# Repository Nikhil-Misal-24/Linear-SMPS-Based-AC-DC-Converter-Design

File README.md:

🔌 AC to DC Converter – PCB Design Project (Detailed Overview)

This project presents the end-to-end design, simulation, and fabrication of a robust AC to DC power supply system, engineered to convert standard 230V AC mains into a stable and regulated DC output suitable for modern electronic applications.

The design emphasizes efficiency, safety, compactness, and reliability, making it ideal for powering sensitive electronic circuits such as microcontrollers, IoT modules, and embedded systems.

⚙️ Working Principle

The system follows a multi-stage power conversion architecture:

Step-Down Stage
High-voltage AC (230V) is reduced to a safer low voltage using a step-down transformer or SMPS module.
Rectification Stage
A bridge rectifier (using 4 diodes) converts the AC signal into a pulsating DC waveform.
Filtering Stage
Large electrolytic capacitors smooth the pulsating DC, reducing ripple and improving signal stability.
Regulation Stage
Voltage regulators like LM7805, LM7812, or LM317 ensure a constant output voltage, irrespective of input fluctuations.
Protection Stage
Includes fuses, current limiting resistors, and thermal shutdown mechanisms to protect against:
Overcurrent
Short circuits
Overheating

✨ Key Features

✔️ Converts 230V AC → Stable DC output (5V / 12V / Adjustable)

✔️ Low ripple output with effective filtering

✔️ Built-in voltage regulation

✔️ Overcurrent & short-circuit protection

✔️ Compact and optimized PCB layout

✔️ Designed for real-world deployment

🧰 Tools & Technologies Used

🖥️ Design Software

KiCad / Eagle / Altium Designer for schematic & PCB layout
ERC & DRC checks for error-free design

🔬 Testing & Debugging

Multimeter – Voltage & continuity testing
Oscilloscope – Ripple and waveform analysis
🔧 Fabrication

PCB etching / manufacturing
Soldering (Through-hole / SMD components)
📐 PCB Design Highlights

Proper ground plane design for noise reduction

Thermal management (heat sinks for regulators)

Track width optimization for high current paths

Isolation between high-voltage AC and low-voltage DC sections

Compact and single-layer / double-layer PCB options

🚀 Applications

🔹 Embedded Systems Power Supply

🔹 IoT Devices (ESP32, Raspberry Pi, sensors)

🔹 Microcontroller Projects (Arduino, PIC, AVR)

🔹 Robotics Circuits

🔹 DIY Electronics Labs

📊 Performance Considerations

Efficiency depends on topology (Linear vs SMPS)

Ripple voltage minimized using high-value capacitors

Heat dissipation handled via heat sinks

Load regulation tested across different current levels

🔮 Future Improvements

Integration of Switch Mode Power Supply (SMPS) for higher efficiency

Addition of digital voltage/current display

PCB miniaturization using SMD components

Smart protection using microcontroller-based monitoring

📌 Conclusion

This project demonstrates a practical implementation of power electronics concepts, combining analog circuit design, PCB layout, and hardware testing into a real-world solution. It serves as a foundational building block for advanced electronic systems and product development.

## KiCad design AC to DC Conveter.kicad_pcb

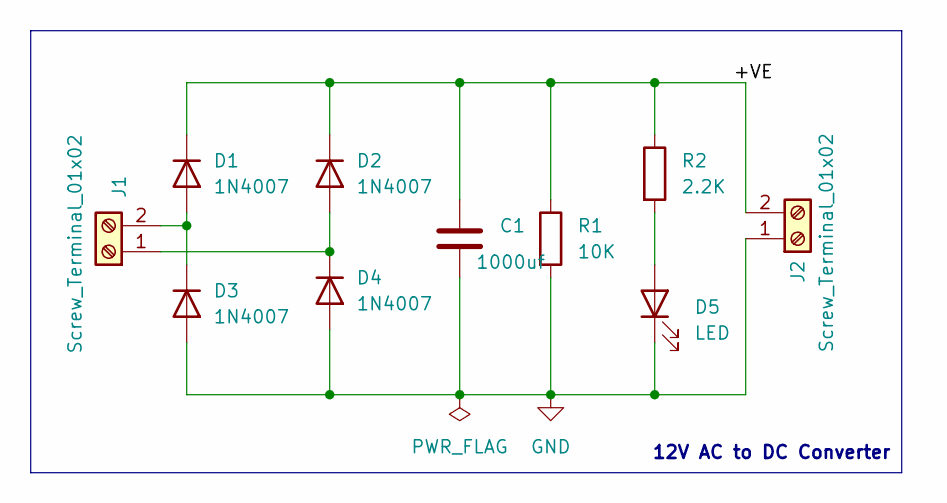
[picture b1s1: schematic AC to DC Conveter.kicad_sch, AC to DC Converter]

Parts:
C1: 1000uf; CP_Radial_D8.0mm_P2.50mm
D1, D2, D3, D4: 1N4007; D_DO-41_SOD81_P10.16mm_Horizontal
D5: LED; LED_D5.0mm
J1, J2: Screw_Terminal_01x02; TerminalBlock_bornier-2_P5.08mm
R1: 10K; R_Axial_DIN0204_L3.6mm_D1.6mm_P7.62mm_Horizontal
R2: 2.2K; R_Axial_DIN0204_L3.6mm_D1.6mm_P7.62mm_Horizontal

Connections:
/+VE: C1.1, D1.1 (K), D2.1 (K), J2.2, R1.1, R2.1
GND: C1.2, D3.2 (A), D4.2 (A), D5.1 (K), J2.1, R1.2
unnamed: D1.2 (A), D3.1 (K), J1.2
unnamed: D2.2 (A), D4.1 (K), J1.1
unnamed: D5.2 (A), R2.2

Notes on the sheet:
12V AC to DC Converter

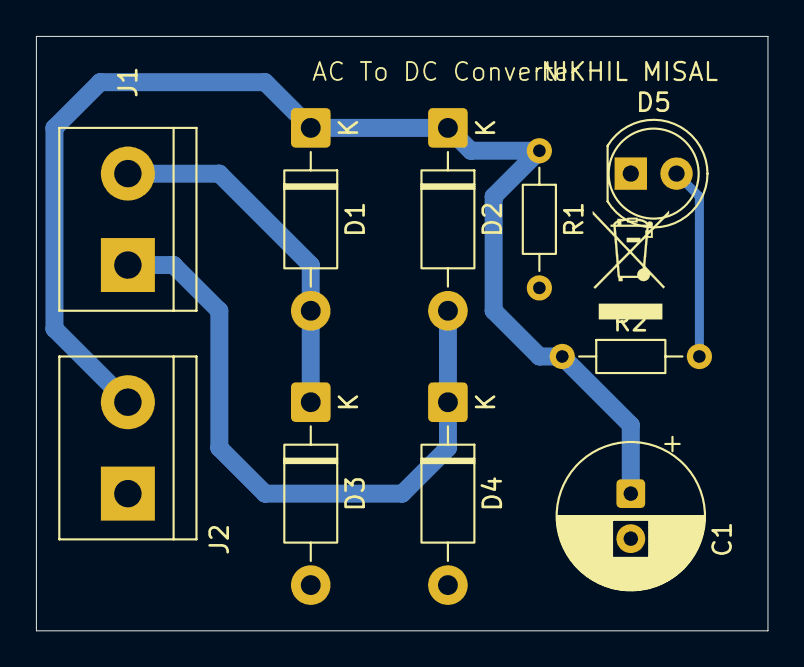
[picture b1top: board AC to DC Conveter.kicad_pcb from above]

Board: 2 copper layers, 40.6 x 33.0 mm, 10 parts (0 on the bottom side), 5 nets.

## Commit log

2026-03-02 Add project overview to README
    This README outlines the AC to DC Converter PCB design project, detailing its features, tools used, and applications.
2026-04-14 Enhance README with detailed project overview and features
    Expanded project overview, features, and applications for AC to DC converter. Added detailed sections on working principle, key features, tools used, performance considerations, future improvements, 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
2026-04-14 Update README with PCB design highlights
    Added additional PCB design considerations for noise reduction and thermal management.
